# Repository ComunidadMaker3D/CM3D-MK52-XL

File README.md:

# Heatbed MK52 XL magnetic
## KiCad PCB layout

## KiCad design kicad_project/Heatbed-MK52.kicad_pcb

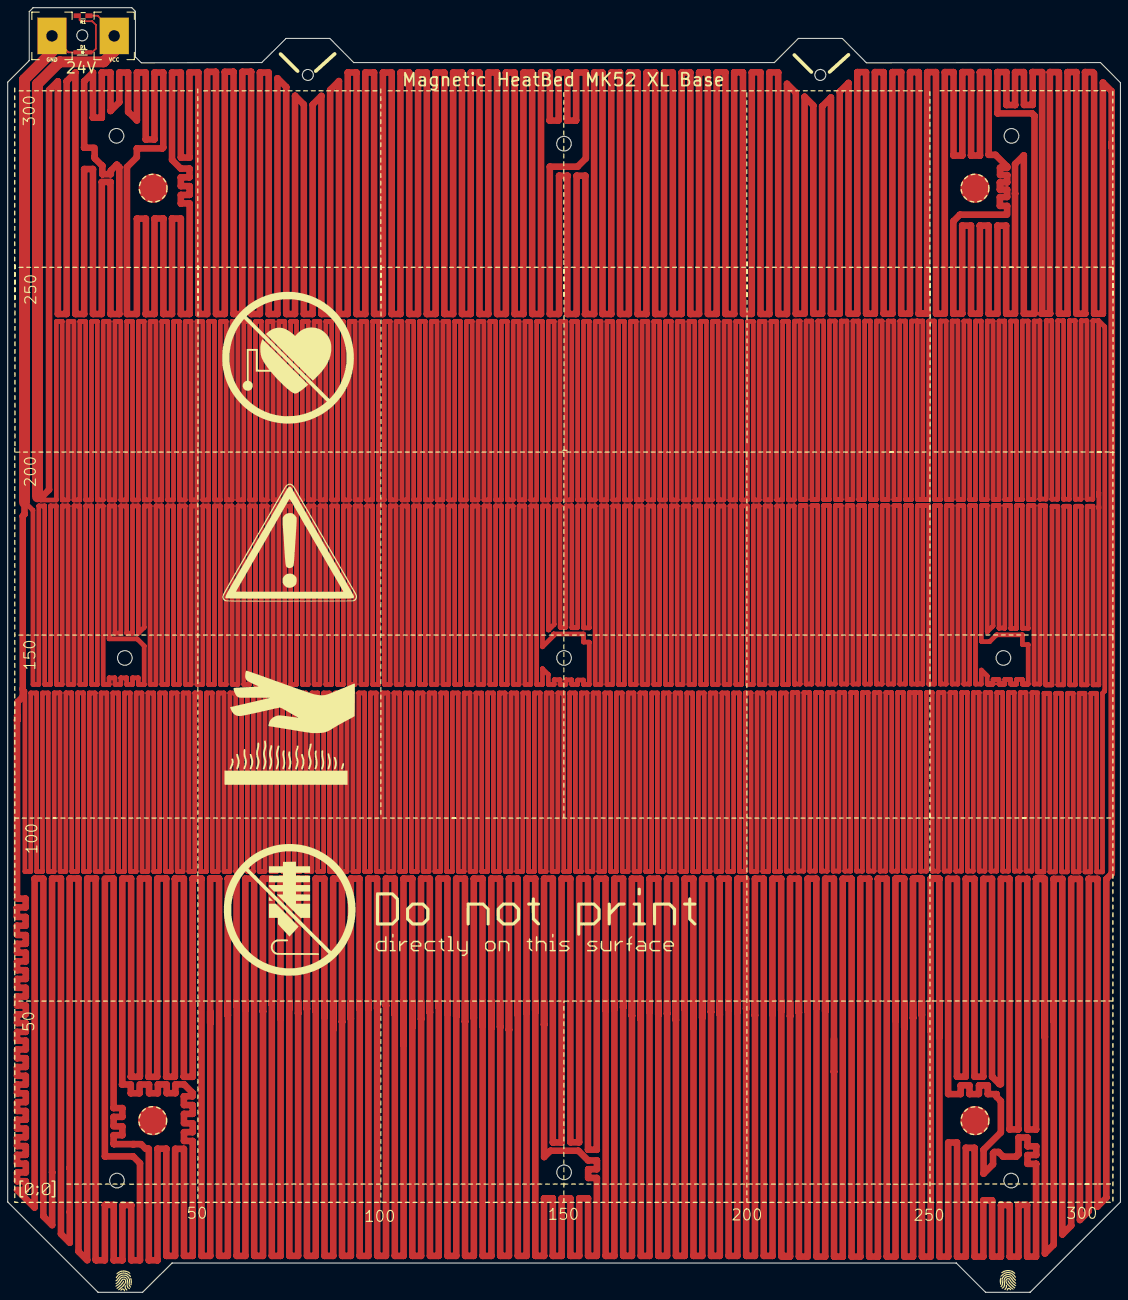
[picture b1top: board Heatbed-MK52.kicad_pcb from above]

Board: 2 copper layers, 304.0 x 351.0 mm, 4 parts (0 on the bottom side), 2 nets.

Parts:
D1: LED_ALT; LED_0805
GND: GND; PCB-Large-pad
R1: 1k; R_0805
VCC: VCC; PCB-Large-pad

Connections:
unnamed: D1.1, GND.1, R1.1, VCC.1
unnamed: D1.2, R1.2

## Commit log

2022-12-24 First commit with all the files related with the kicad project and design of the MK52 XL
2023-01-12 Add files via upload
    Modified to make room for PCB cutting as it was too close to pads.
2023-01-12 Make room for PCB cutting
    Modified to make room for PCB cutting as it was too close to pads.
2023-01-15 Updated with SMD components and schema
    Updated with SMD components and schema

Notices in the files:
parts and their libraries:
Licenssed under GPL v3: B.SilkS
